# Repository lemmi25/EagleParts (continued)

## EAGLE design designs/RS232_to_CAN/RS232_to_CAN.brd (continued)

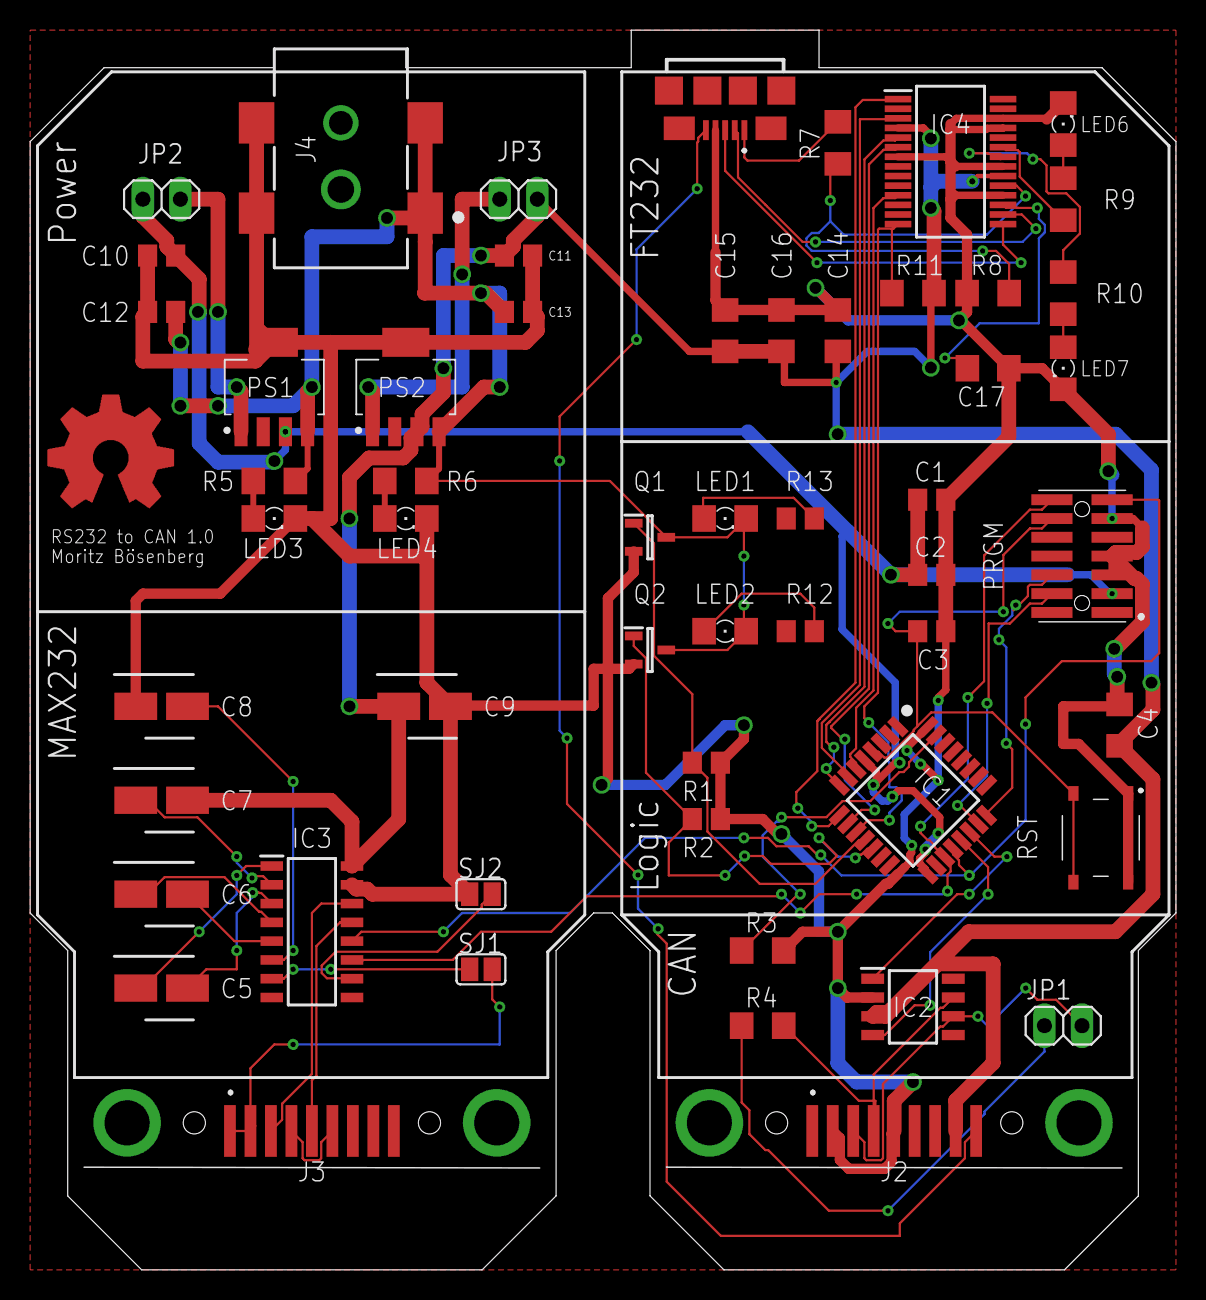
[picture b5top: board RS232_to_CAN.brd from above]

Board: 2 copper layers, 77.5 x 83.8 mm, 55 parts (0 on the bottom side), 50 nets.

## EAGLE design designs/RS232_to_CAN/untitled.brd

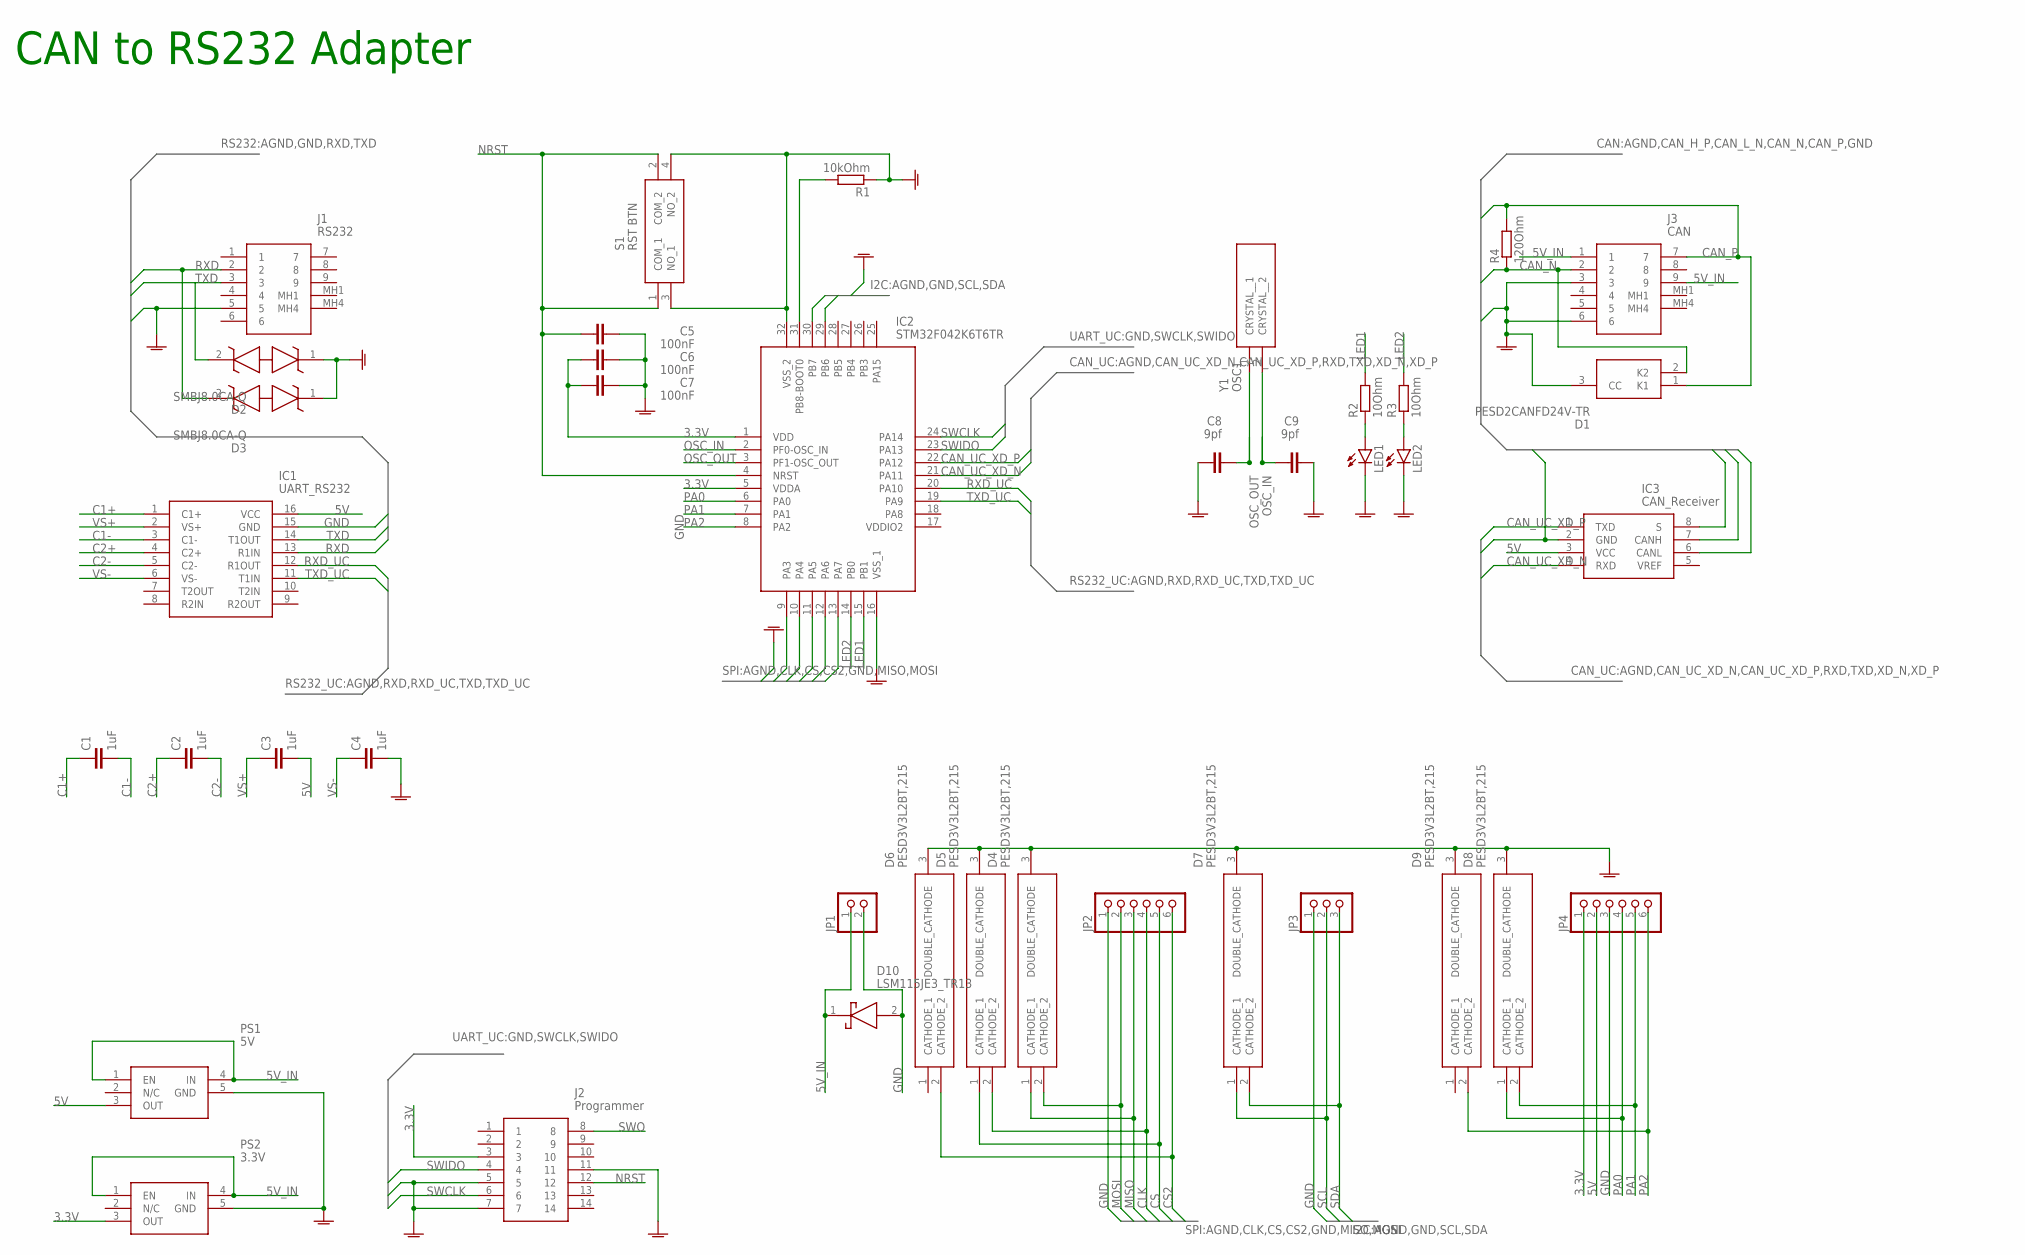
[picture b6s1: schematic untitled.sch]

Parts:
C1, C2, C3, C4: 1uF; C0805
C5, C6, C7: 100nF; C0805
C8, C9: 9pf; C0805
D1: PESD2CANFD24V-TR; SOT95P230X110-3N
D2, D3: SMBJ8.0CA-Q; DIONM5436X244N
D4, D5, D6, D7, D8, D9: PESD3V3L2BT,215; SOT95P230X110-3N
D10: LSM115JE3_TR13; DIOM5436X330N
IC1: UART_RS232; SOIC127P600X175-16N
IC2: STM32F042K6T6TR; QFP80P900X900X160-32N
IC3: CAN_Receiver; SOIC127P600X175-8N
J1: RS232; K202XHTE9SN
J2: Programmer; FTSH10701LDVKA
J3: CAN; K202XHTE9SN
JP1: PINHD-1X2; 1X02
JP2, JP4: PINHD-1X6; 1X06
JP3: PINHD-1X3; 1X03
LED1, LED2: LED_805SML0805; SML0805
PS1: 5V; SOT150P700X160-5N
PS2: 3.3V; SOT150P700X160-5N
R1: 10kOhm; R0805
R2, R3: 10Ohm; R0805
R4: 120Ohm; R0805
S1: RST BTN; PTS526SM15SMTR2LFS
Y1: OSC1; CM7VT1A32768KHZ7PF100PPMTAQC

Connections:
3.3V: C6.1, C7.1, IC2.1 (VDD), IC2.5 (VDDA), J2.3, JP4.1, PS2.3 (OUT)
5V: C3.2, IC1.16 (VCC), IC3.3 (VCC), JP4.2, PS1.3 (OUT)
5V_IN: D10.1 (K), J3.1, J3.9, JP1.1, PS1.1 (EN), PS1.4 (IN), PS2.1 (EN), PS2.4 (IN)
C1+: C1.1, IC1.1 (C1+)
C1-: C1.2, IC1.3 (C1-)
C2+: C2.1, IC1.4 (C2+)
C2-: C2.2, IC1.5 (C2-)
CAN_N: D1.2 (K2), IC3.6 (CANL), J3.2, R4.1
CAN_P: D1.1 (K1), IC3.7 (CANH), J3.7, R4.2
CAN_UC_XD_N: IC2.21 (PA11), IC3.4 (RXD)
CAN_UC_XD_P: IC2.22 (PA12), IC3.1 (TXD)
CLK: D5.2 (CATHODE_2), IC2.11 (PA5), JP2.4
CS: D5.1 (CATHODE_1), IC2.10 (PA4), JP2.5
CS2: D6.2 (CATHODE_2), IC2.9 (PA3), JP2.6
GND: C4.2, C5.2, C6.2, C7.2, C8.1, C9.2, D1.3 (CC), D2.1, D3.1, D4.3 (DOUBLE_CATHODE), D5.3 (DOUBLE_CATHODE), D6.3 (DOUBLE_CATHODE), D7.3 (DOUBLE_CATHODE), D8.3 (DOUBLE_CATHODE), D9.3 (DOUBLE_CATHODE), D10.2 (A), IC1.15 (GND), IC2.16 (VSS_1), IC2.32 (VSS_2), IC3.2 (GND), IC3.8 (S), J1.5, J2.5, J2.7, J2.11, J3.3, J3.6, JP1.2, JP2.1, JP3.1, JP4.3, LED1.C, LED2.C, PS1.5 (GND), PS2.5 (GND), R1.1, S1.3 (NO_1), S1.4 (NO_2)
LED1: IC2.15 (PB1), R2.2
LED2: IC2.14 (PB0), R3.2
MISO: D4.1 (CATHODE_1), IC2.12 (PA6), JP2.3
MOSI: D4.2 (CATHODE_2), IC2.13 (PA7), JP2.2
unnamed: LED1.A, R2.1
unnamed: LED2.A, R3.1
unnamed: IC2.31 (PB8-BOOT0), R1.2
NRST: C5.1, IC2.4 (NRST), J2.12, S1.1 (COM_1), S1.2 (COM_2)
OSC_IN: C9.1, IC2.2 (PF0-OSC_IN), Y1.2 (CRYSTAL__2)
OSC_OUT: C8.2, IC2.3 (PF1-OSC_OUT), Y1.1 (CRYSTAL__1)
PA0: D8.1 (CATHODE_1), IC2.6 (PA0), JP4.4
PA1: D8.2 (CATHODE_2), IC2.7 (PA1), JP4.5
PA2: D9.2 (CATHODE_2), IC2.8 (PA2), JP4.6
RXD: D3.2, IC1.13 (R1IN), J1.2
RXD_UC: IC1.12 (R1OUT), IC2.20 (PA10)
SCL: D7.1 (CATHODE_1), IC2.29 (PB6), JP3.2
SDA: D7.2 (CATHODE_2), IC2.30 (PB7), JP3.3
SWCLK: IC2.24 (PA14), J2.6
SWIDO: IC2.23 (PA13), J2.4
SWO: J2.8
TXD: D2.2, IC1.14 (T1OUT), J1.3
TXD_UC: IC1.11 (T1IN), IC2.19 (PA9)
VS+: C3.1, IC1.2 (VS+)
VS-: C4.1, IC1.6 (VS-)

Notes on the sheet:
CAN to RS232 Adapter

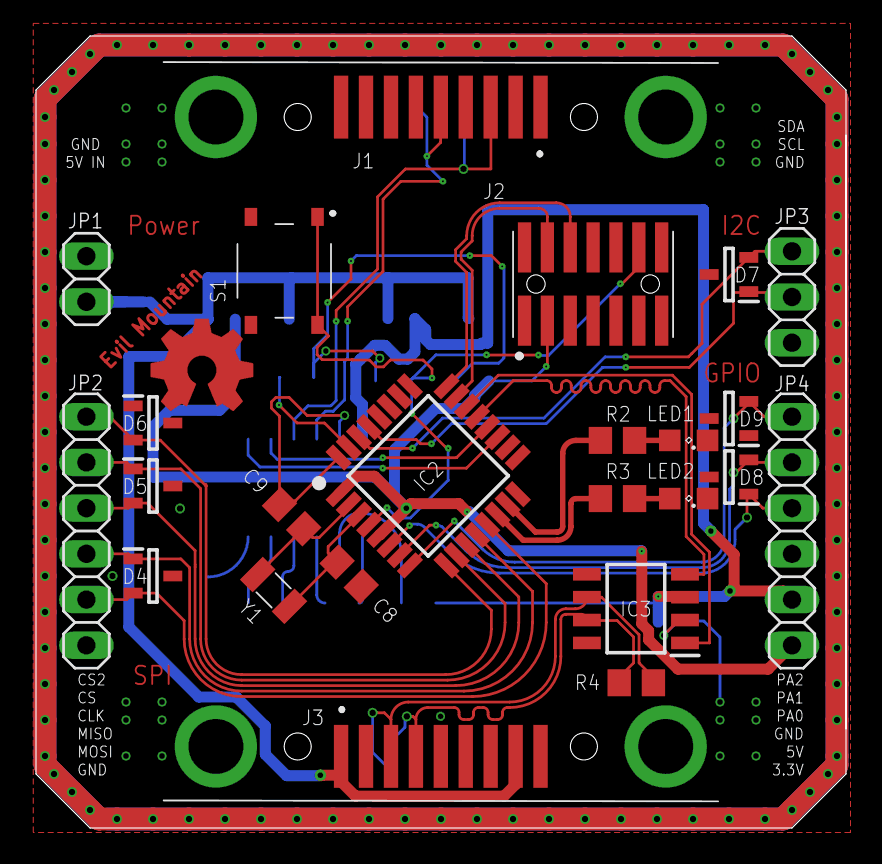
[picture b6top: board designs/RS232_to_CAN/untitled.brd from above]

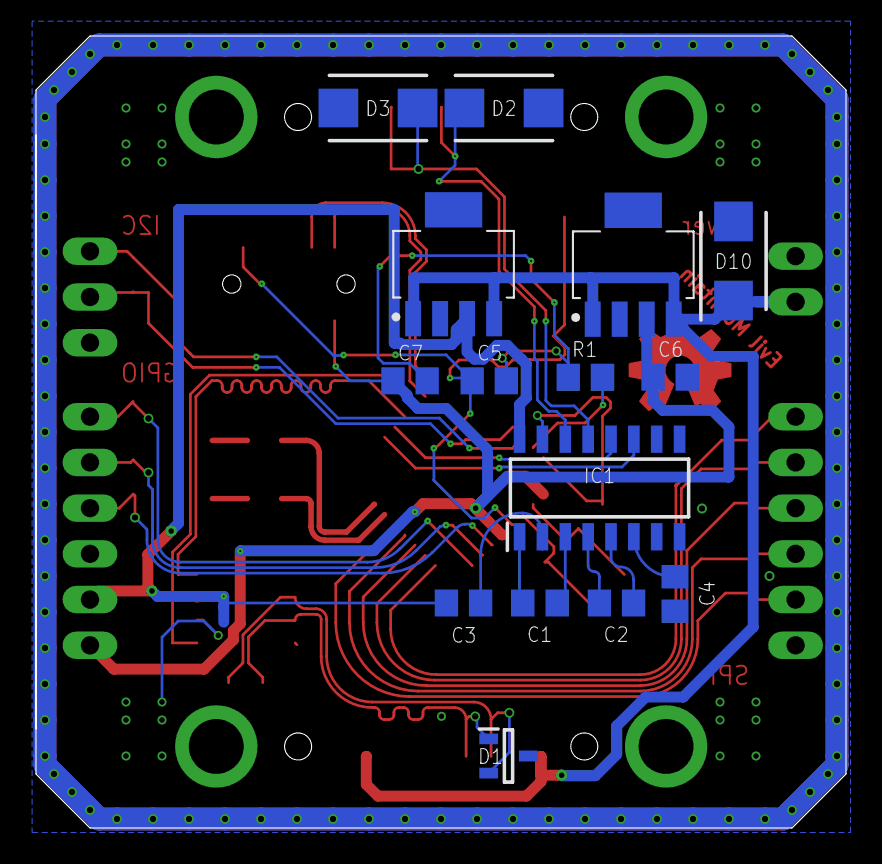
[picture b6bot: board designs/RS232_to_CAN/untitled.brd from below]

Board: 2 copper layers, 45.0 x 44.0 mm, 39 parts (15 on the bottom side), 38 nets.

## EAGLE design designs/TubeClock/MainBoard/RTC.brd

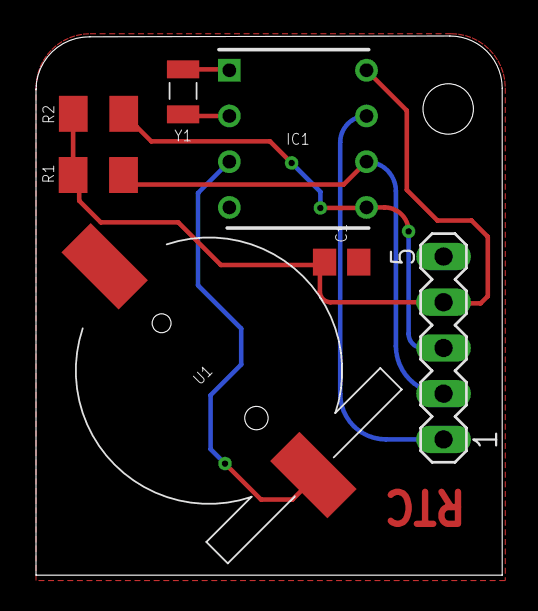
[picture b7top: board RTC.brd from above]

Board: 2 copper layers, 25.9 x 30.0 mm, 7 parts (0 on the bottom side), 8 nets.

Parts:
C1: 0.1uF; C0805
IC1: DS1307N+; DIP762W56P254L938H457Q8N
R1, R2: 2.2K; M1206
SV1: MA05-1
U1: S8411-45R; S8411-45R_1
Y1: CM7V-T1A-32.768K-9PF-20PPM-TA-; CM7VT1A32768KHZ125PF10PPMTBQC

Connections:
GND: C1.1, IC1.4, SV1.5, U1.2
unnamed: IC1.1, Y1.2
unnamed: IC1.2, Y1.1
SCL: IC1.6, R1.2, SV1.2
SDA: IC1.5, R2.2, SV1.3
SQW/OUT: IC1.7, SV1.1
VBAT: IC1.3, U1.1
VCC: C1.2, IC1.8, R1.1, R2.1, SV1.4
